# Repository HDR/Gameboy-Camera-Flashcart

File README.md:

## Make sure you read the License (Attribution-NonCommercial-ShareAlike 4.0 International)

If you want to support me for free (and get 5 USD in new user credit) you can use my PCBWay [Referral link](https://www.pcbway.com/setinvite.aspx?inviteid=388393) when signing up on PCBWay

**Make sure you read the License!**

**Flashing:**

Flashing has only been tested with a [GBxCart](https://www.insidegadgets.com/projects/gbxcart-rw/), flashing both 1MB sections requires [this custom software](GBxCart_RW_GB_Camera_2x1MB_Flasher.zip), which is a modified version of InsideGadget's 2x2MB MBC3 software, or [FlashGBX](https://github.com/lesserkuma/FlashGBX/releases) v3.2 and above.

**BOM:**

| Reference | Part Number | Description |
|-|-|-|
| C1 | [4x4.5mm 22uF](https://www.aliexpress.com/item/32377971645.html) | 22uF 16V 4x4.5 Electrolytic Capacitor |
| C2, C3, C4, C12, C13 | [TCC0603X7R104J500CT](https://www.lcsc.com/product-detail/Multilayer-Ceramic-Capacitors-MLCC-SMD-SMT_CCTC-TCC0603X7R104J500CT_C282518.html) | 100nF 0603 Capacitor |
| C5, C6, C7, C8, C9, C10, C11 | [CC0402KRX7R7BB104](https://lcsc.com/product-detail/Multilayer-Ceramic-Capacitors-MLCC-SMD-SMT_YAGEO-CC0402KRX7R7BB104_C60474.html) | 100nF 0402 Capacitor |
| C14, C15 | [CC0603JRNPO9BN220](https://www.lcsc.com/product-detail/Multilayer-Ceramic-Capacitors-MLCC-SMD-SMT_YAGEO-CC0603JRNPO9BN220_C105620.html) | 22pF 0603 Capacitor |
| R1 | [RC0603JR-071KL](https://www.lcsc.com/product-detail/Chip-Resistor-Surface-Mount_YAGEO-RC0603JR-071KL_C14676.html) | 1K Ω 0603 Resistor |
| D1 | Diode | Harvest D2 from original cartridge |
| J1 | [B9B-ZR-SM4-TF](https://www.aliexpress.com/item/32920487056.html) | Camera Connector, Harvest or buy (JST ZH1.5MM 9 Pin) |
| SW1 | [K3-1296S-E1](https://www.lcsc.com/product-detail/Slide-Switches_Korean-Hroparts-Elec-K3-1296S-E1_C128955.html)| SPDT Switch (For 2x1MB Rom Switching) |
| U1 | MAC-GBD | Harvest U1 from original cartridge |
| U2 | [AM29F016](https://www.aliexpress.com/item/33043533022.html) | 2MB Flash |
| U3 | [FM28V100](https://www.aliexpress.com/item/4001322883101.html) | 1MB FRAM |
| U4 | [TPRT9013-33G](https://www.lcsc.com/product-detail/Linear-Voltage-Regulators-LDO_TECH-PUBLIC-TPRT9013-33GB_C587158.html) | 3.3V Voltage Regulator |

[Interactive BOM](https://martinrefseth.com/ibom/Game%20Boy%20Camera%20Flashcart)

Makes use of [djedditt's](https://github.com/djedditt/s) [gamepak footprint](https://github.com/djedditt/kicad-gamepaks)

Looking for a ready to use flashcart? check out InsideGadgets custom flashcart, the [Insidegadgets' PicNRec AIO](https://shop.insidegadgets.com/product/gameboy-camera-picnrec-aio/)

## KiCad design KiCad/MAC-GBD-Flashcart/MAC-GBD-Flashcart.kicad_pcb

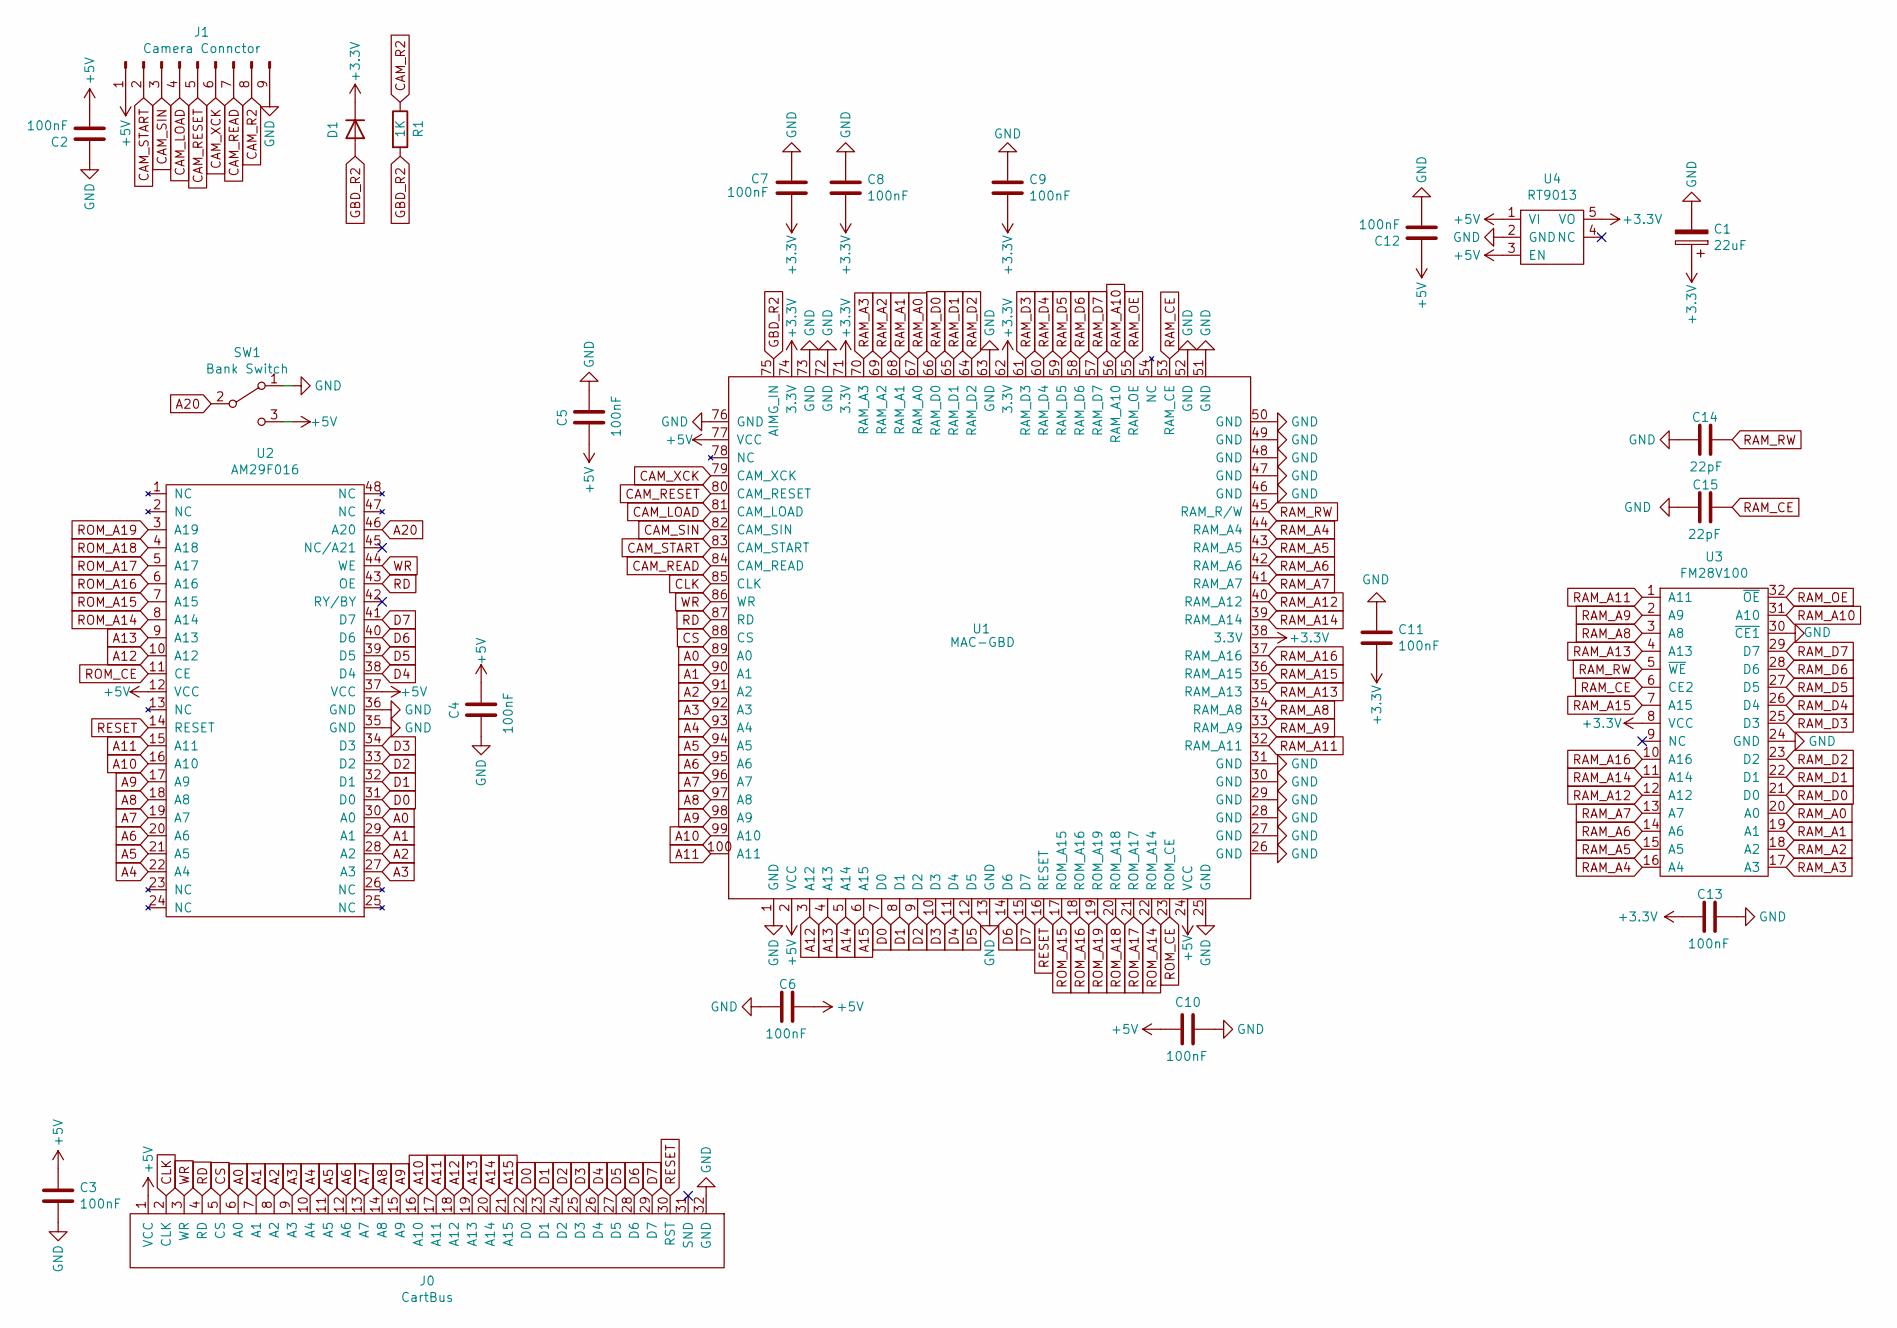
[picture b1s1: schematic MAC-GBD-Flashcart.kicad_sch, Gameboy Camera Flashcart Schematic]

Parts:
C1: 22uF; CP_Elec_4x4.5
C2, C3, C4, C12, C13: 100nF; C_0603_1608Metric
C5, C6, C7, C8, C9, C10, C11: 100nF; C_0402_1005Metric
C14, C15: 22pF; C_0603_1608Metric
D1: Diode; D_SOD-123
J0: CartBus; GameBoy_GamePak_CGB-002_P1.50mm_Edge
J1: Camera Connctor; JST_B9B-ZR-SM4-TF
R1: 1K; R_0603_1608Metric
SW1: Bank Switch; SW_SPDT-K3-1296S-E1
U1: MAC-GBD; LQFP-100_14x14mm_P0.5mm
U2: AM29F016; AM29F0XX
U3: FM28V100; TSOP-I-32_11.8x8mm_P0.5mm
U4: RT9013; SOT-23-5

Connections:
+3V3: C1.1, C7.1, C8.2, C9.2, C11.2, C13.2, D1.1 (K), U1.38 (3.3V), U1.62 (3.3V), U1.71 (3.3V), U1.74 (3.3V), U3.8 (VCC), U4.5 (VO)
+5V: C2.2, C3.1, C4.2, C5.1, C6.1, C10.2, C12.1, J0.1 (VCC), J1.1, SW1.3 (B), U1.2 (VCC), U1.24 (VCC), U1.77 (VCC), U2.12 (VCC), U2.37 (VCC), U4.1 (VI), U4.3 (EN); also elsewhere on the board
A0: J0.6 (A0), U1.89 (A0), U2.30 (A0); also elsewhere on the board
A1: J0.7 (A1), U1.90 (A1), U2.29 (A1); also elsewhere on the board
A2: J0.8 (A2), U1.91 (A2), U2.28 (A2); also elsewhere on the board
A3: J0.9 (A3), U1.92 (A3), U2.27 (A3); also elsewhere on the board
A4: J0.10 (A4), U1.93 (A4), U2.22 (A4); also elsewhere on the board
A5: J0.11 (A5), U1.94 (A5), U2.21 (A5); also elsewhere on the board
A6: J0.12 (A6), U1.95 (A6), U2.20 (A6); also elsewhere on the board
A7: J0.13 (A7), U1.96 (A7), U2.19 (A7); also elsewhere on the board
A8: J0.14 (A8), U1.97 (A8), U2.18 (A8); also elsewhere on the board
A9: J0.15 (A9), U1.98 (A9), U2.17 (A9); also elsewhere on the board
A10: J0.16 (A10), U1.99 (A10), U2.16 (A10); also elsewhere on the board
A11: J0.17 (A11), U1.100 (A11), U2.15 (A11); also elsewhere on the board
A12: J0.18 (A12), U1.3 (A12), U2.10 (A12); also elsewhere on the board
A13: J0.19 (A13), U1.4 (A13), U2.9 (A13); also elsewhere on the board
A14: J0.20 (A14), U1.5 (A14); also elsewhere on the board
A15: J0.21 (A15), U1.6 (A15); also elsewhere on the board
CAM_LOAD: J1.4, U1.81 (CAM_LOAD)
CAM_R2: J1.8, R1.1
CAM_READ: J1.7, U1.84 (CAM_READ)
CAM_RESET: J1.5, U1.80 (CAM_RESET)
CAM_SIN: J1.3, U1.82 (CAM_SIN)
CAM_START: J1.2, U1.83 (CAM_START)
CAM_XCK: J1.6, U1.79 (CAM_XCK)
CLK: J0.2 (CLK~), U1.85 (CLK); also elsewhere on the board
CS: J0.5 (CS), U1.88 (CS); also elsewhere on the board
D0: J0.22 (D0), U1.7 (D0), U2.31 (D0); also elsewhere on the board
D1: J0.23 (D1), U1.8 (D1), U2.32 (D1); also elsewhere on the board
D2: J0.24 (D2), U1.9 (D2), U2.33 (D2); also elsewhere on the board
D3: J0.25 (D3), U1.10 (D3), U2.34 (D3); also elsewhere on the board
D4: J0.26 (D4), U1.11 (D4), U2.38 (D4); also elsewhere on the board
D5: J0.27 (D5), U1.12 (D5), U2.39 (D5); also elsewhere on the board
D6: J0.28 (D6), U1.14 (D6), U2.40 (D6); also elsewhere on the board
D7: J0.29 (D7), U1.15 (D7), U2.41 (D7); also elsewhere on the board
GBD_R2: D1.2 (A), R1.2, U1.75 (AIMG_IN)
unnamed: SW1.2 (C), U2.46 (A20)
RAM_A0: U1.67 (RAM_A0), U3.20 (A0)
RAM_A1: U1.68 (RAM_A1), U3.19 (A1)
RAM_A2: U1.69 (RAM_A2), U3.18 (A2)
RAM_A3: U1.70 (RAM_A3), U3.17 (A3)
RAM_A4: U1.44 (RAM_A4), U3.16 (A4)
RAM_A5: U1.43 (RAM_A5), U3.15 (A5)
RAM_A6: U1.42 (RAM_A6), U3.14 (A6)
RAM_A7: U1.41 (RAM_A7), U3.13 (A7)
RAM_A8: U1.34 (RAM_A8), U3.3 (A8)
RAM_A9: U1.33 (RAM_A9), U3.2 (A9)
RAM_A10: U1.56 (RAM_A10), U3.31 (A10)
RAM_A11: U1.32 (RAM_A11), U3.1 (A11)
RAM_A12: U1.40 (RAM_A12), U3.12 (A12)
RAM_A13: U1.35 (RAM_A13), U3.4 (A13)
RAM_A14: U1.39 (RAM_A14), U3.11 (A14)
RAM_A15: U1.36 (RAM_A15), U3.7 (A15)
RAM_A16: U1.37 (RAM_A16), U3.10 (A16)
RAM_D0: U1.66 (RAM_D0), U3.21 (D0)
RAM_D1: U1.65 (RAM_D1), U3.22 (D1)
RAM_D2: U1.64 (RAM_D2), U3.23 (D2)
RAM_D3: U1.61 (RAM_D3), U3.25 (D3)
RAM_D4: U1.60 (RAM_D4), U3.26 (D4)
RAM_D5: U1.59 (RAM_D5), U3.27 (D5)
RAM_D6: U1.58 (RAM_D6), U3.28 (D6)
RAM_D7: U1.57 (RAM_D7), U3.29 (D7)
RAM_OE: U1.55 (RAM_OE), U3.32 (~OE)
RAM_RW: C14.1, U1.45 (RAM_R/W), U3.5 (~WE)
RD: J0.4 (RD), U1.87 (RD), U2.43 (OE); also elsewhere on the board
RESET: J0.30 (RST), U1.16 (RESET), U2.14 (RESET); also elsewhere on the board
ROM_A14: U1.22 (ROM_A14), U2.8 (A14)
ROM_A15: U1.17 (ROM_A15), U2.7 (A15)
ROM_A16: U1.18 (ROM_A16), U2.6 (A16)
ROM_A17: U1.21 (ROM_A17), U2.5 (A17)
ROM_A18: U1.20 (ROM_A18), U2.4 (A18)
ROM_A19: U1.19 (ROM_A19), U2.3 (A19)
ROM_CE: U1.23 (ROM_CE), U2.11 (CE)
WR: J0.3 (WR), U1.86 (WR), U2.44 (WE); also elsewhere on the board

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
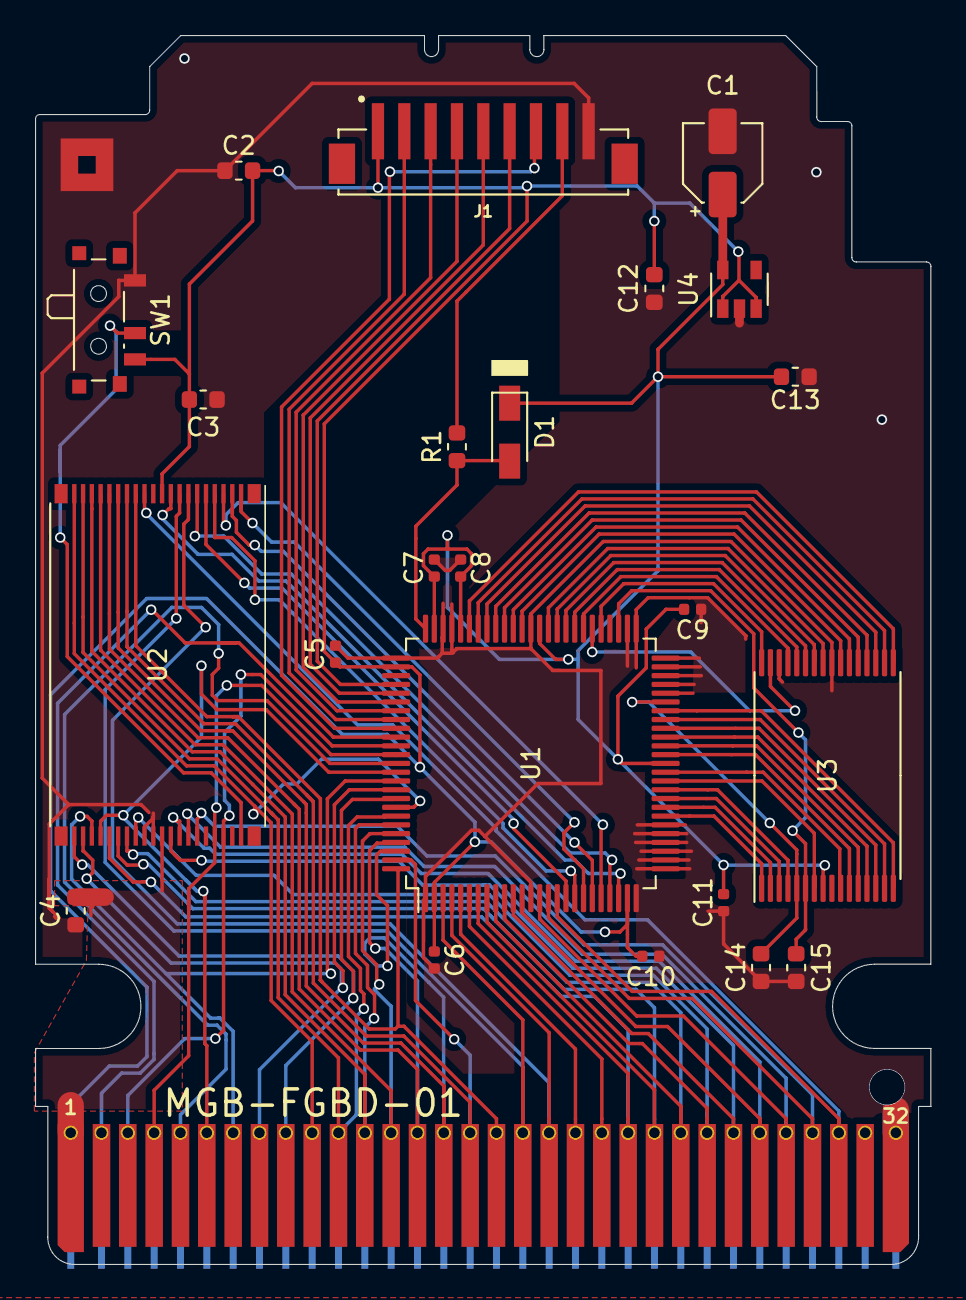
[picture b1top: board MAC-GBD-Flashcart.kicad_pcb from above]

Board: 2 copper layers, 51.0 x 70.0 mm, 25 parts (0 on the bottom side), 76 nets.

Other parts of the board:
PAD*: Nintendo_3x3_GNDPad
U0: CartBus; GameBoy_GamePak_CGB-002_P1.50mm_Edge

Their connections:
+5V: U0.1; also elsewhere on the board
A0: U0.6; also elsewhere on the board
A1: U0.7; also elsewhere on the board
A2: U0.8; also elsewhere on the board
A3: U0.9; also elsewhere on the board
A4: U0.10; also elsewhere on the board
A5: U0.11; also elsewhere on the board
A6: U0.12; also elsewhere on the board
A7: U0.13; also elsewhere on the board
A8: U0.14; also elsewhere on the board
A9: U0.15; also elsewhere on the board
A10: U0.16; also elsewhere on the board
A11: U0.17; also elsewhere on the board
A12: U0.18; also elsewhere on the board
A13: U0.19; also elsewhere on the board
A14: U0.20; also elsewhere on the board
A15: U0.21; also elsewhere on the board
CLK: U0.2; also elsewhere on the board
CS: U0.5; also elsewhere on the board
D0: U0.22; also elsewhere on the board
D1: U0.23; also elsewhere on the board
D2: U0.24; also elsewhere on the board
D3: U0.25; also elsewhere on the board
D4: U0.26; also elsewhere on the board
D5: U0.27; also elsewhere on the board
D6: U0.28; also elsewhere on the board
D7: U0.29; also elsewhere on the board
RD: U0.4; also elsewhere on the board
RESET: U0.30; also elsewhere on the board
WR: U0.3; also elsewhere on the board

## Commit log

2020-08-30 Create Gameboy Camera Schematic 1.0.pdf
    Add original board schematic
2021-02-11 Create LICENSE
2021-07-31 Add License
2021-07-31 Update Schematic
    Update schematic to fix some issues.
2021-09-23 Add board image
2021-09-24 Add Software
2022-01-07 Update Schematic
    Add missing pin name for pin 75
2022-05-13 Create Gitingore, add sensor datasheet
2022-06-20 Add advanced pcb link
2023-11-08 Release Project Files

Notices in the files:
KiCad/MAC-GBD-Flashcart/MAC-GBD-Flashcart.kicad_sch:
Licensed under CC BY-NC-SA 4.0
